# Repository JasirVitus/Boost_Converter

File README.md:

# Boost_Converter
Simple step-up DC/DC converter based on LM3478 controller. Output voltage can be adjusted with a trimmer.
## Converter specification: ##
  - **Input voltage range:** 8-13V
  - **Nominal output voltage:** 20V
  - **Maximal output current:** 1A
  - **Maximal output power:** 20W
  - **Switching frequency:** 200KHz
  - **Voltage ripple:** In progress
  - **Current ripple:** In progress

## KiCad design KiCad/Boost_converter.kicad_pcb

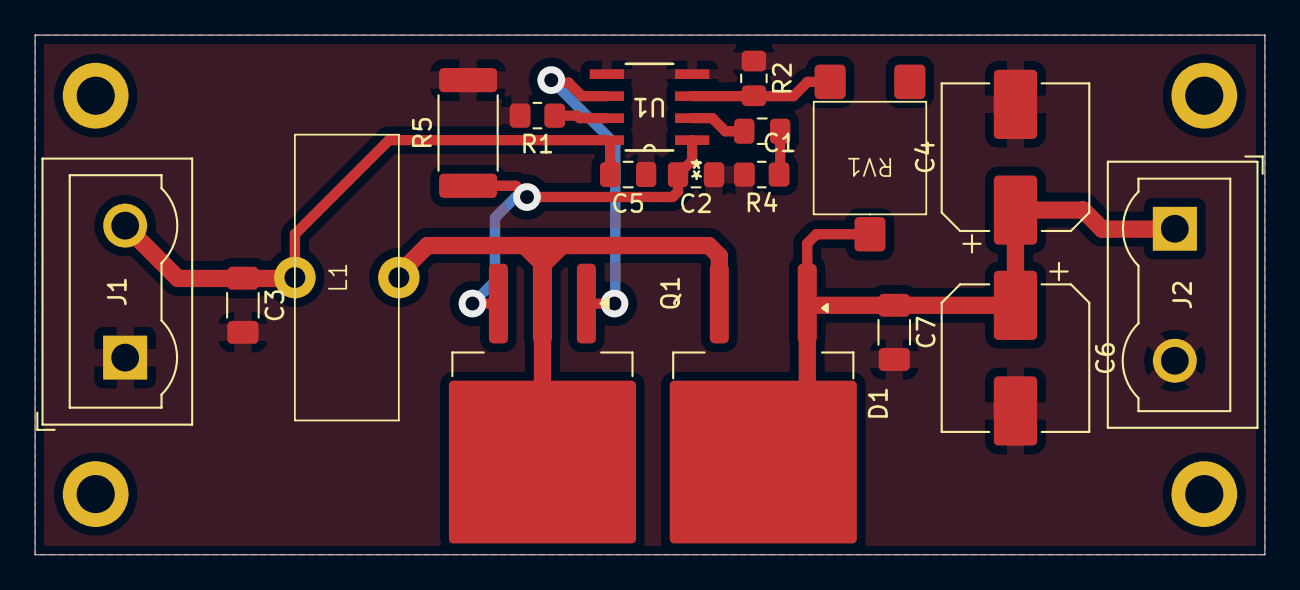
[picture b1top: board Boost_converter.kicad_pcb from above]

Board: 2 copper layers, 71.0 x 30.0 mm, 18 parts (0 on the bottom side), 10 nets.

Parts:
C1: C; C_0805_2012Metric_Pad1.18x1.45mm_HandSolder
C2, C5: 100n; C_0805_2012Metric_Pad1.18x1.45mm_HandSolder
C3, C7: 10u; C_1206_3216Metric_Pad1.33x1.80mm_HandSolder
C4, C6: 68u; CP_Elec_8x6.7
D1: D_Schottky; TO-263-2_TabPin1
J1, J2: Screw_Terminal_01x02; TerminalBlock_Wuerth_691311400102_P7.62mm
L1: L; L_16x6mm
Q1: IRF740; TO-263-3_TabPin2
R1, R2: 40k; R_0805_2012Metric_Pad1.20x1.40mm_HandSolder
R4: R; R_0805_2012Metric_Pad1.20x1.40mm_HandSolder
R5: 20m; R_2512_6332Metric_Pad1.40x3.35mm_HandSolder
RV1: R_Potentiometer_Trim; Trimmer_6.5mm
U1: LM3478MA/NOPB; M08A

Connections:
GND: C2.1, C3.2, C4.2, C5.1, C6.2, C7.2, J1.1, J2.2, R1.2, R2.1, R4.2, R5.2, U1.4 (AGND), U1.5 (PGND)
unnamed: C1.1, R4.1
unnamed: D1.2 (A), L1.2, Q1.2 (D)
unnamed: C4.1, C6.1, C7.1, D1.1 (K), J2.1, RV1.2
unnamed: C3.1, C5.2, J1.2, L1.1, U1.8 (VIN)
unnamed: Q1.1 (G), U1.6 (DR)
unnamed: C2.2, Q1.3 (S), R5.1, U1.1 (ISEN)
unnamed: C1.2, U1.2 (COMP)
unnamed: R1.1, U1.7 (FA/SD)
unnamed: R2.2, RV1.3, U1.3 (FB)

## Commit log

2025-11-04 Add files via upload
    First commit
2025-11-04 Update README.md
    Added photo
